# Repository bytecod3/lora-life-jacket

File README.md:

# lora-life-jacket
Electronic device for life jackets with LORA data transmission

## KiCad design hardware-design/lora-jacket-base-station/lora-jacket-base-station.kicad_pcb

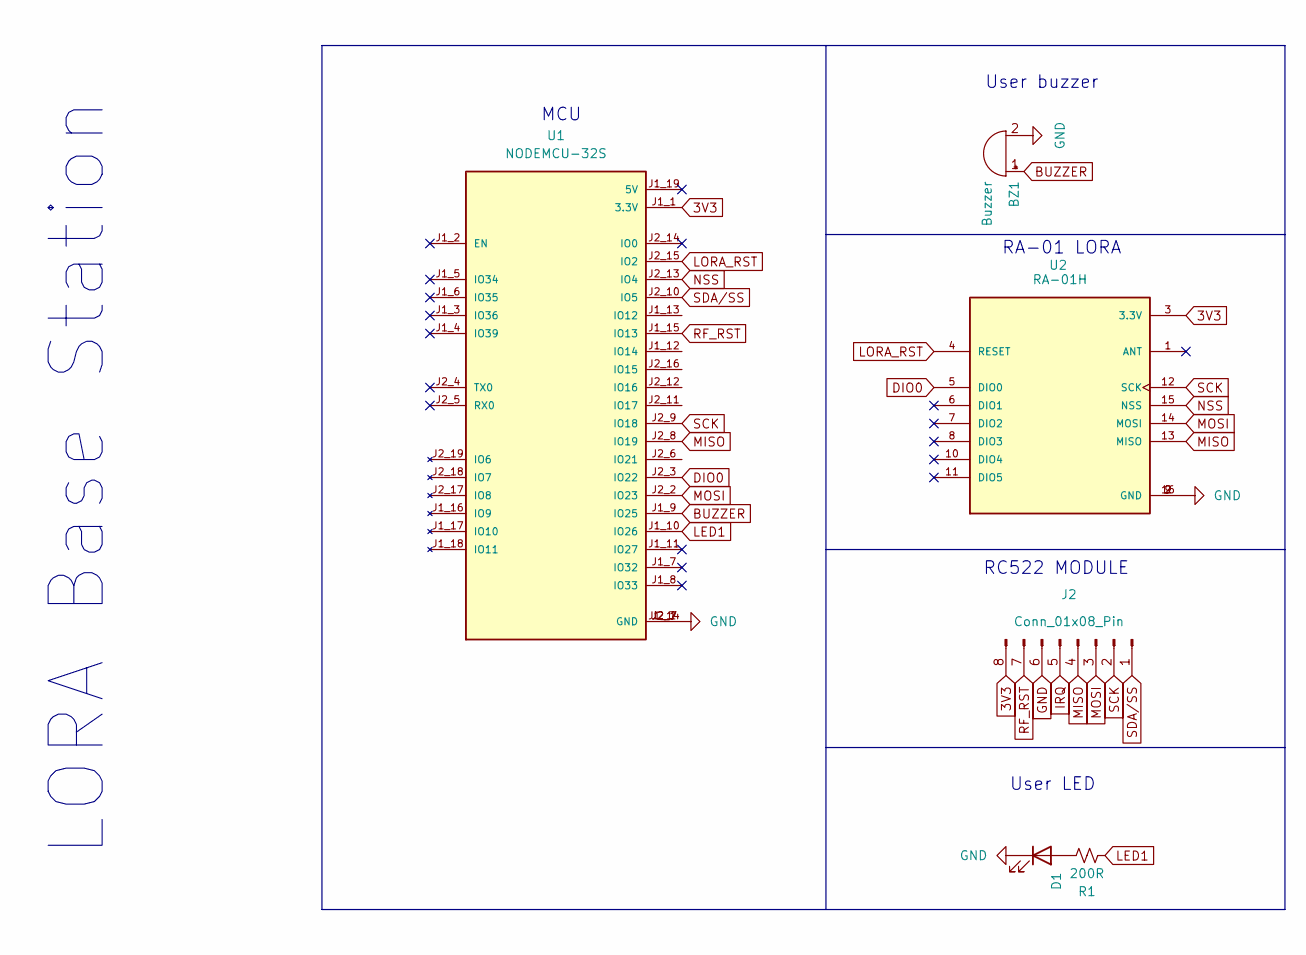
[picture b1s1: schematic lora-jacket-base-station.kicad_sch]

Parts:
BZ1: Buzzer; MagneticBuzzer_ProSignal_ABI-010-RC
D1: GREEN; LED_D3.0mm
J2: Conn_01x08_Pin; PinHeader_1x08_P2.54mm_Vertical
R1: 200R; R_Axial_DIN0516_L15.5mm_D5.0mm_P25.40mm_Horizontal
U1: NODEMCU-32S; MODULE_NODEMCU-32S; PARTREV V1
U2: RA-01H; XCVR_RA-01H; PARTREV V1.0

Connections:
3V3: J2.8, U1.J1_1 (3.3V), U2.3 (3.3V)
BUZZER: BZ1.1 (+), U1.J1_9 (IO25)
DIO0: U1.J2_3 (IO22), U2.5 (DIO0)
GND: BZ1.2 (-), D1.1 (K), J2.6, U1.J1_14 (GND), U1.J2_1 (GND), U1.J2_7 (GND), U2.2 (GND), U2.9 (GND), U2.16 (GND)
IRQ: J2.5
LED1: R1.1, U1.J1_10 (IO26)
LORA_RST: U1.J2_15 (IO2), U2.4 (RESET)
MISO: J2.4, U1.J2_8 (IO19), U2.13 (MISO)
MOSI: J2.3, U1.J2_2 (IO23), U2.14 (MOSI)
NSS: U1.J2_13 (IO4), U2.15 (NSS)
unnamed: D1.2 (A), R1.2
RF_RST: J2.7, U1.J1_15 (IO13)
SCK: J2.2, U1.J2_9 (IO18), U2.12 (SCK)
SDA/SS: J2.1, U1.J2_10 (IO5)

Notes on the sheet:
RA-01 LORA
LORA Base Station
RC522 MODULE
MCU
User buzzer
User LED

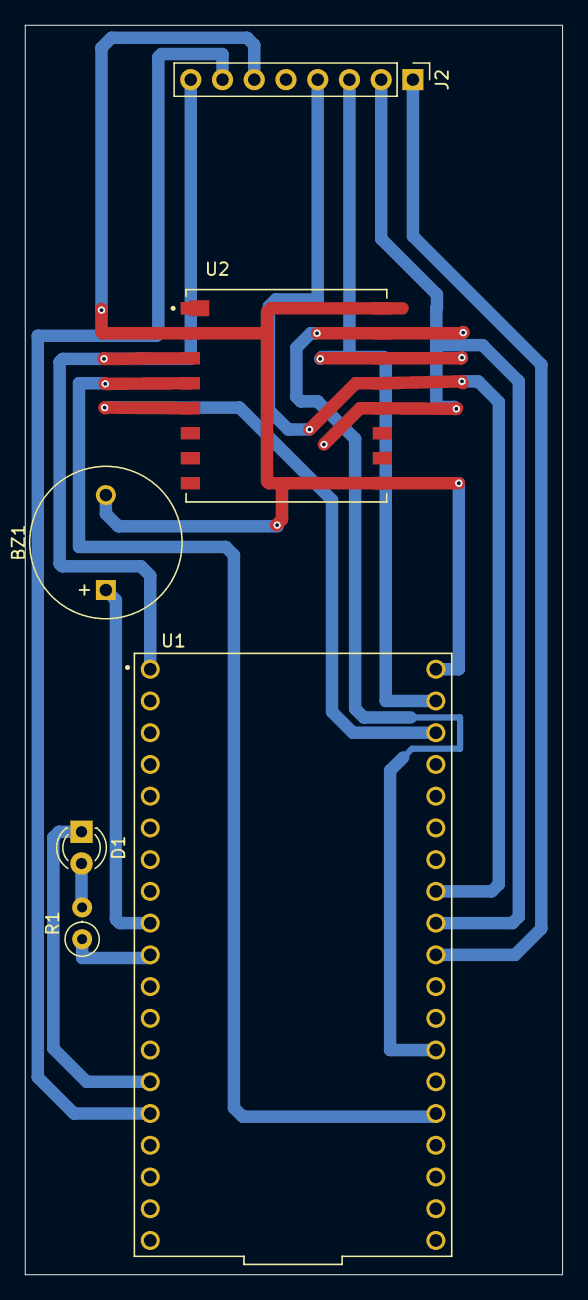
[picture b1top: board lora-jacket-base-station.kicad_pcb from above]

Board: 2 copper layers, 43.0 x 100.0 mm, 6 parts (0 on the bottom side), 13 nets.

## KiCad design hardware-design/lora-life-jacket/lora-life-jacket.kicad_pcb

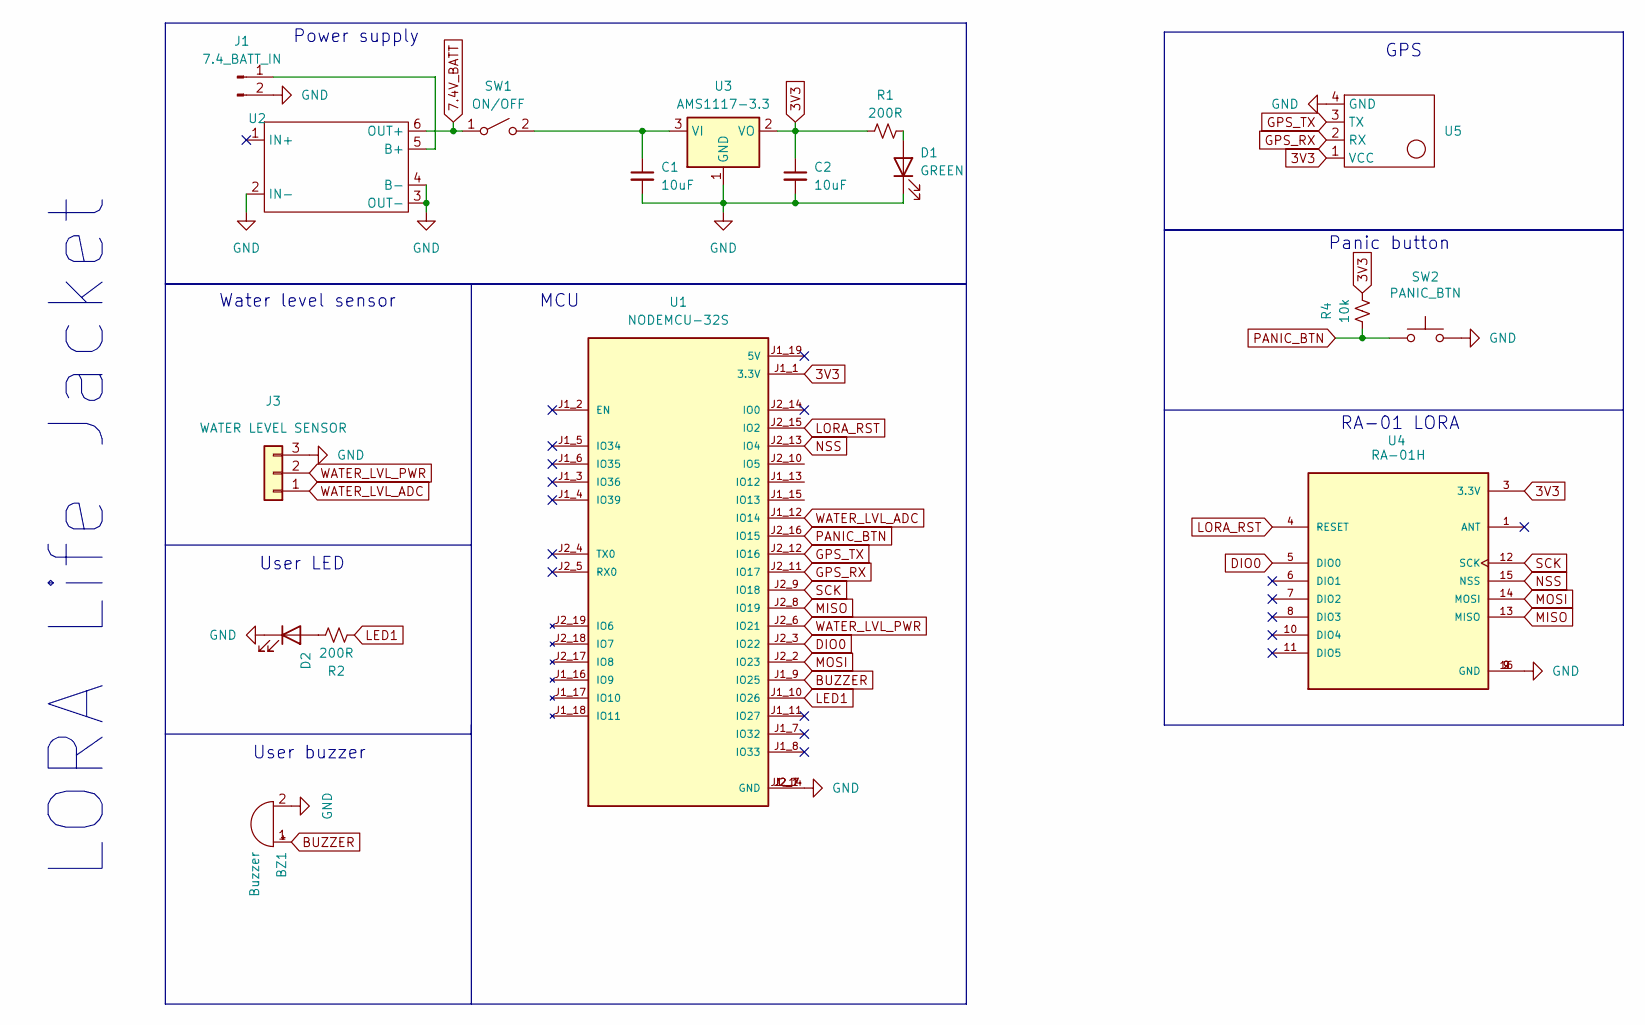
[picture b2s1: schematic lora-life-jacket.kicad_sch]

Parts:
BZ1: Buzzer; MagneticBuzzer_ProSignal_ABI-010-RC
C1, C2: 10uF; CP_Radial_D8.0mm_P3.80mm
D1, D2: GREEN; LED_D3.0mm
J1: 7.4_BATT_IN; PinHeader_1x02_P2.54mm_Vertical
J3: WATER LEVEL SENSOR; PinHeader_1x03_P2.54mm_Vertical
R1, R2: 200R; R_Axial_DIN0309_L9.0mm_D3.2mm_P15.24mm_Horizontal
R4: 10k; R_Axial_DIN0309_L9.0mm_D3.2mm_P15.24mm_Horizontal
SW1: ON/OFF; SW_Push_2P2T_Toggle_CK_PVA2OAH5xxxxxxV2
SW2: PANIC_BTN; SW_Tactile_Straight_KSL0Axx1LFTR
U1: NODEMCU-32S; MODULE_NODEMCU-32S; PARTREV V1
U2: TP4056-MODULE
U3: AMS1117-3.3; SOT-223-3_TabPin2
U4: RA-01H; XCVR_RA-01H; PARTREV V1.0
U5: NEO-6M-GPS-MODULE

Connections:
3V3: C2.1, R1.1, R4.2, U1.J1_1 (3.3V), U3.2 (VO), U4.3 (3.3V), U5.1 (VCC)
7.4V_BATT: SW1.1 (A), U2.6 (OUT+)
BUZZER: BZ1.1 (+), U1.J1_9 (IO25)
DIO0: U1.J2_3 (IO22), U4.5 (DIO0)
GND: BZ1.2 (-), C1.2, C2.2, D1.1 (K), D2.1 (K), J1.2, J3.3, SW2.2, U1.J1_14 (GND), U1.J2_1 (GND), U1.J2_7 (GND), U2.2 (IN-), U2.3 (OUT-), U2.4 (B-), U3.1 (GND), U4.2 (GND), U4.9 (GND), U4.16 (GND), U5.4 (GND)
GPS_RX: U1.J2_11 (IO17), U5.2 (RX)
GPS_TX: U1.J2_12 (IO16), U5.3 (TX)
LED1: R2.1, U1.J1_10 (IO26)
LORA_RST: U1.J2_15 (IO2), U4.4 (RESET)
MISO: U1.J2_8 (IO19), U4.13 (MISO)
MOSI: U1.J2_2 (IO23), U4.14 (MOSI)
NSS: U1.J2_13 (IO4), U4.15 (NSS)
unnamed: D1.2 (A), R1.2
unnamed: D2.2 (A), R2.2
unnamed: J1.1, U2.5 (B+)
unnamed: C1.1, SW1.2 (B), U3.3 (VI)
PANIC_BTN: R4.1, SW2.1, U1.J2_16 (IO15)
SCK: U1.J2_9 (IO18), U4.12 (SCK)
WATER_LVL_ADC: J3.1, U1.J1_12 (IO14)
WATER_LVL_PWR: J3.2, U1.J2_6 (IO21)

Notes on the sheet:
Water level sensor
User LED
Power supply
User buzzer
LORA Life Jacket
MCU
RA-01 LORA
Panic button
GPS

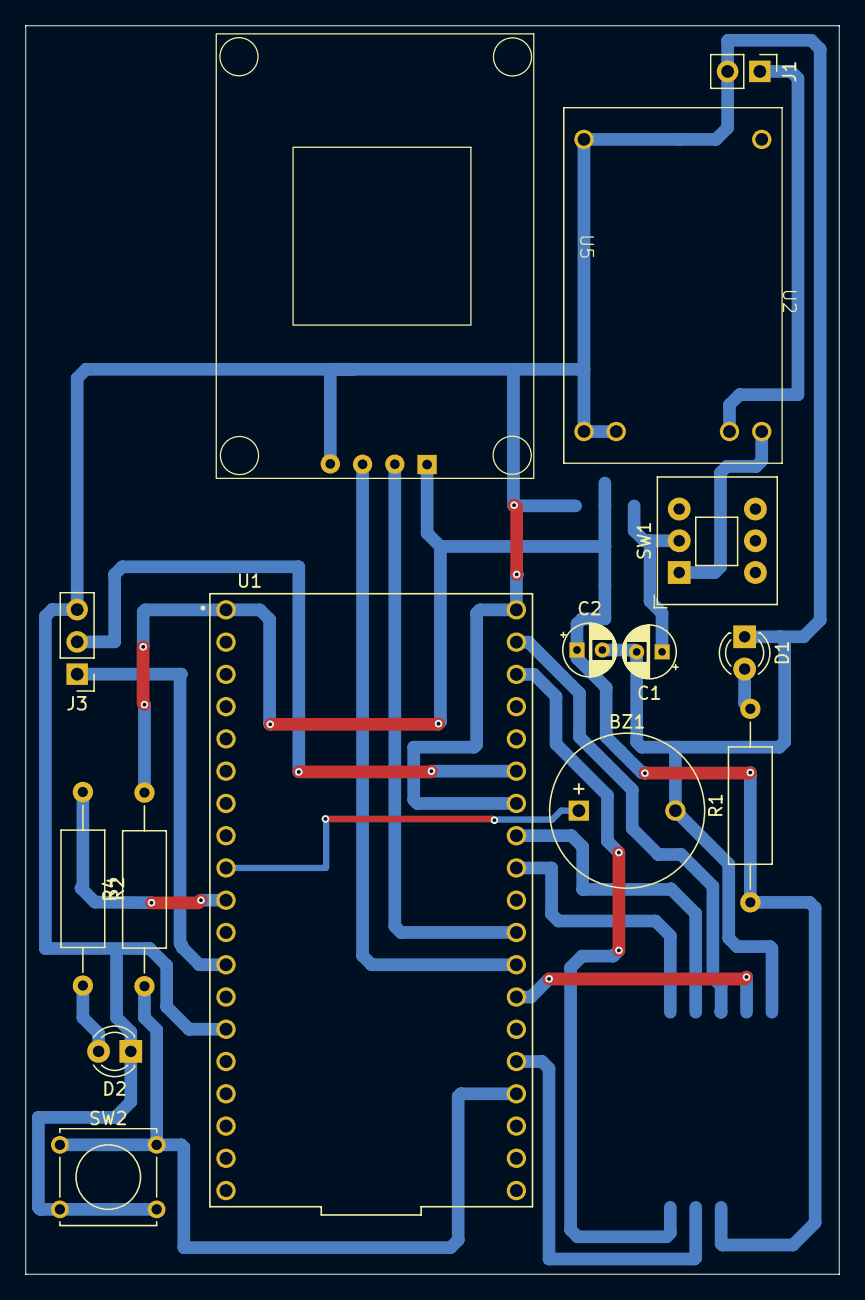
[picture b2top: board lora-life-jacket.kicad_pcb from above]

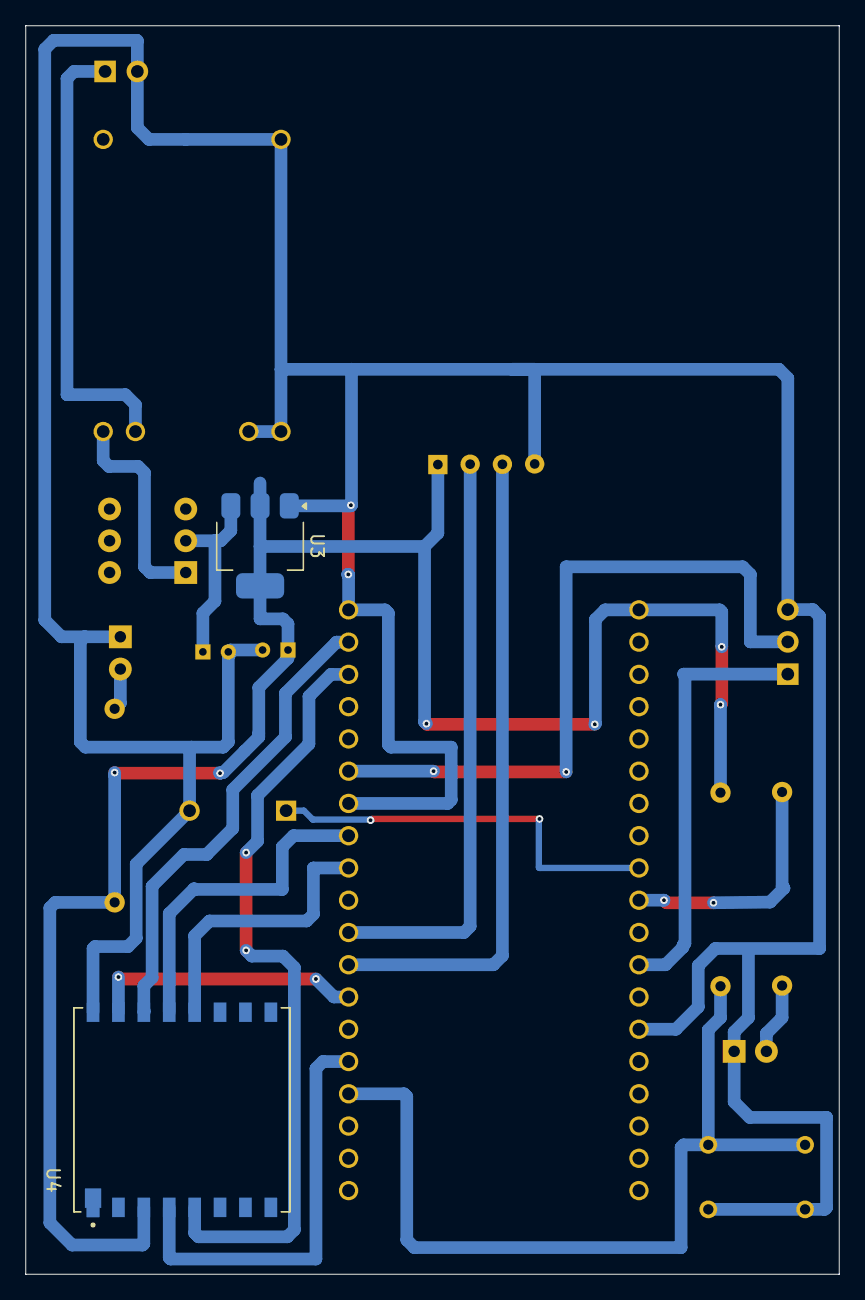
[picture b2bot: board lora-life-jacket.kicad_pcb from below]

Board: 2 copper layers, 64.0 x 98.3 mm, 17 parts (2 on the bottom side), 20 nets.

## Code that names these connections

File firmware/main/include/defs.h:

#ifndef DEFS_H
#define DEFS_H

#define DEBUG 1

#if DEBUG
#define debug(x)   Serial.print(x);
#define debugln(x)  Serial.println(x);
#define debugf(x, y) Serial.printf(x, y)

#else 
#define debug(x) 
#define debugln(x)  
#endif // END DEBUG

// pin definitions
#define LORA_CS 4
#define LORA_RST    2
#define LORA_DIO    22
#define LORA_FREQUENCY 433E6
#define LORA_DELAY 10

#define BAUDRATE 115200
#define LED_BLINK   400

// RFID reader Pins
#define RFID_RST    12
#define RFID_CS     5

// other pin defs
#define LED1 26
#define PANIC_BUTTON 15

// water level pin
#define WATER_LEVEL_PWR 21
#define WATER_LEVEL_ADC_PIN 14

// GPS serial
#define GPS_RX 16
#define GPS_TX 17
#define GPS_BAUD 9600

#define BUZZER 25


#endif

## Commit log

2024-11-21 adds firmware init functions
2024-11-22 adds water level init
2024-11-22 adds btn debounce
2024-11-22 resolves TinyGPS lib
2024-11-22 adds RFID read function
2024-11-26 adds finished schematic
2024-11-26 adds base station
2024-12-01 adds PCB tracks
2024-12-01 adds lora receive
2024-12-01 change LORA frequency
2024-12-01 updates lora message packet
2024-12-04 adds base station PCB
2024-12-14 updates loar packet
2025-01-05 removes reader on jacket
2025-01-05 adds panic button interrupt
2025-01-05 adds jacket issue message
2025-01-05 Final working code
2025-01-05 final working code with LED
2025-01-25 final firmware changes
2025-01-25 updates message send
